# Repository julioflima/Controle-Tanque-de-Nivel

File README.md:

# Controle Tanque de Nível
## Projeto de Controle de Sistemas Dinâmicos - Engenharia Elétrica  - UFC

  Este projeto destina-se ao desenvolvimento de um controle de tanque de nível utilizando os conceitos de malha fechada. Como conrolador e sensor foram escolhidos respectivamente, o ATMEGA168-P e o HC-SR04.

  Os sistemas automáticos de níveis de água atualmente estão presentes em boa parte no cotidiano da vida humana, sejam em industrias ou mesmo nas casas, tendo em vista os conceitos de reutilização ou captação de água. Para controlar estes tipos de sistemas, geralmente utilizam-se de sensores de nível para acionamento da bomba e o controle pode ser feito a partir de um controlador PID ou por histerese, por exemplo. O relatório referente a este projeto se limitará à um controle realizado com base na histerese de sistemas de controle, nos quais os procedimentos serão apresentados mais adiante. A figura abaixo mostra um exemplo esquemático de um sistema hidráulico controlado pela bomba.

  Para o sistema controlado, a histerese é implementada na forma dinâmica de um determinado atraso da saída em referência com a entrada, desde que esta seja lentamente variável. Este tipo de histerese é uma relação de dependência de taxas, ou seja, pode funcionar com sistemas que necessitem de armazenamento durável de memória. Esta técnica como controlador serve basicamente para filtragem de sinais a fim de que se obtenha uma saída mais lenta de acordo com a memória armazenada de um sinal mais recente. 
Em um sistema baseado em ações liga/desliga, este controle reduz a vida útil ou afeta os dispositivos conectados a este sistema. Por isso, a utilização da técnica de histerese torna-se interessante para sistemas do tipo, resultando, assim, em uma seleção de uma determinada faixa, por exemplo com temperatura, como mostra abaixo.

  A IHM desenvolvida, teve como intuito a facilidade na hora de interagir na mudança do valor de referência e na visualização do nível atual do tanque independentemente da medição analógica, essa por meio de um duto transparente. Nela foi utilizada um display LCD 16x2, onde é possível a verificação dos valores. Dois botões para mudança no valor da referência. Dois barramentos, um destinado ao sensor ultrassônico, e o outro destinado a placa de driver. Uma saída seria, onde os valores de PWM, nível do tanque e valore de referência, são enviados ao computador para análise. Assim como o micro controlador ATMEGA328-P, responsável pelo controle e aquisição de dados. O esquemático e a placa discorrida nesta seção encontra-se nos anexos do relatório.

  O sensor utilizado neste projeto é o sensor ultrassônico HC-SR04, utilizado para medir distâncias entre 2cm até 4m. Com o intuito de fixação na estrutura desenvolvia, o sensor foi encapsulado em um case como mostra a figura abaixo. O esquemático discorrido nesta seção, assim como mais detalhes encontra-se nos anexos do relatório.

  O driver representa a parte de potência de um projeto, sendo este responsável pelo chaveamento de uma alta corrente, pois o controlador não suporta esse nível de potência, sendo assim indispensável. A placa de controle desenvolvida segue abaixo na figura abaixo.

  Segue abaixo os gráficos relativos a dinâmica desse sistema, com o controle desenvolvido até então. Em verde o PWM, em vermelho a referência e em azul a elevação do nível da água.

## FORK IT!

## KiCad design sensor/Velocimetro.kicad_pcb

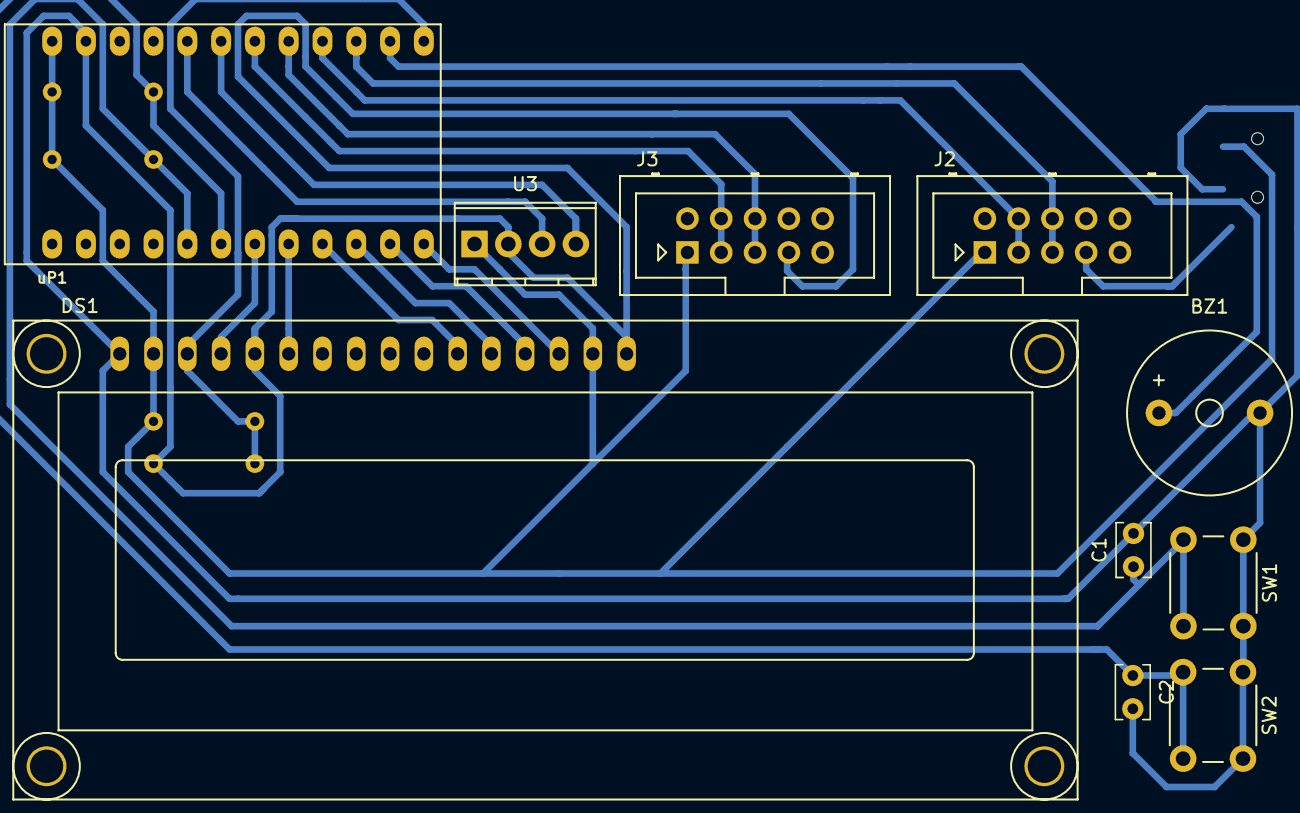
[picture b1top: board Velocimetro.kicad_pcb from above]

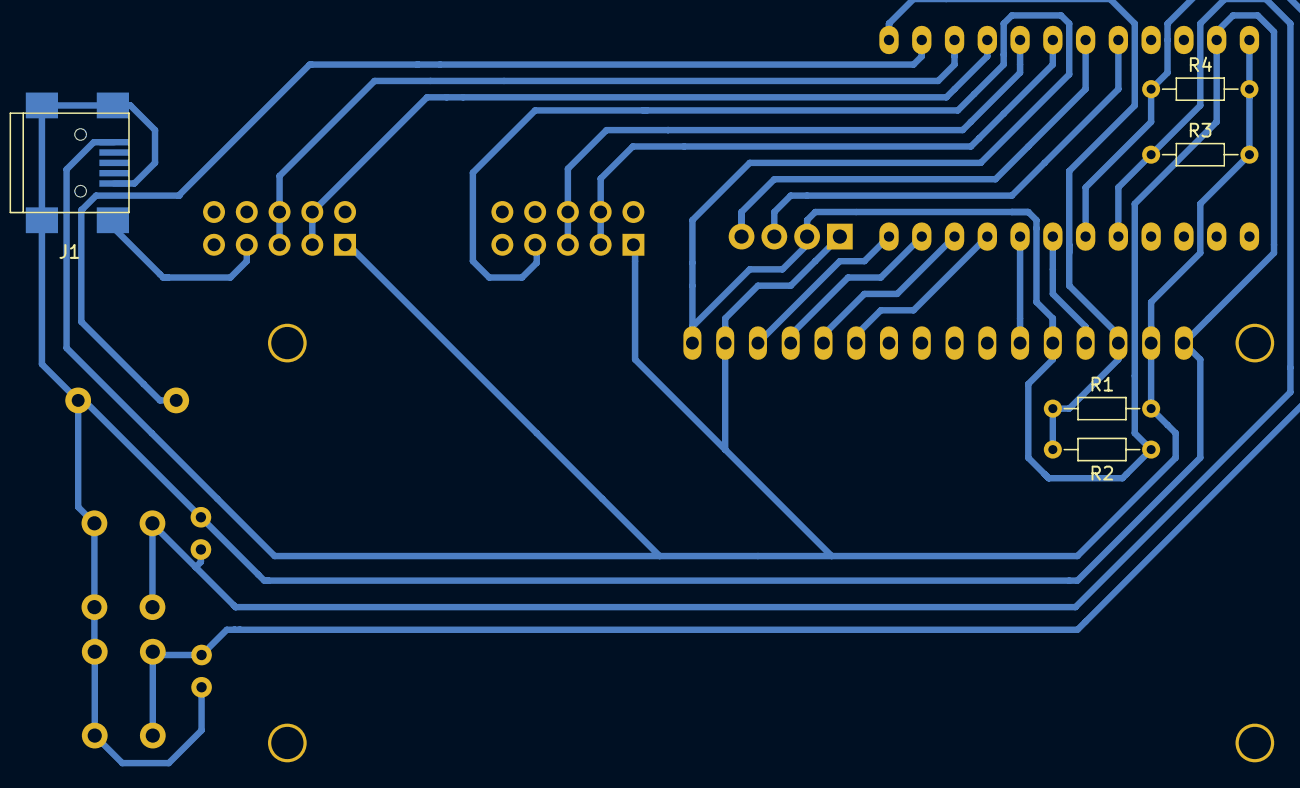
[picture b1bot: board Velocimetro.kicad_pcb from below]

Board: 2 copper layers, 15 parts (5 on the bottom side), 18 nets.

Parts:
BZ1: Buzzer; Buzzer_12x9.5RM7.6
C1, C2: 100n; C_Rect_L4.0mm_W2.5mm_P2.50mm
DS1: LCD16X2; WC1602A
J1: USB_OTG; USB_Mini-B
J2, J3: Conn_02x05_Odd_Even; Multicomp_MC9A12-1034_2x05x2.54mm_Straight
R1: 22k; R_Axial_DIN0204_L3.6mm_D1.6mm_P7.62mm_Horizontal
R2, R3, R4: 1k; R_Axial_DIN0204_L3.6mm_D1.6mm_P7.62mm_Horizontal
SW1, SW2: SW_DIP_x01; SW_PUSH_6mm
U3: HC-05; TerminalBlock_Phoenix_MPT-2.54mm_4pol
uP1: arduino_pro_mini; pro_mini

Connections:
+5V: DS1.2, DS1.15, J1.1, J2.1, J3.1, R1.2, R3.2, R4.2, U3.1, uP1.24
GND: BZ1.2, C1.2, C2.2, DS1.1, DS1.5, DS1.16, J1.5, J1.6, J2.7, J3.7, R2.1, SW1.1, SW2.1, U3.2, uP1.23
blue-RXD: U3.4, uP1.19
blue-TXD: U3.3, uP1.20
btn-1: C1.1, R3.1, SW1.2, uP1.5
btn-2: C2.1, R4.1, SW2.2, uP1.6
buzzer: BZ1.1, uP1.14
d4: DS1.11, uP1.9
d5: DS1.12, uP1.10
d6: DS1.13, uP1.11
d7: DS1.14, uP1.12
e: DS1.6, uP1.8
rs: DS1.4, uP1.7
uS01-2: J2.3, J2.4, uP1.16
uS01-3: J2.5, J2.6, uP1.15
uS02-2: J3.3, J3.4, uP1.18
uS02-3: J3.5, J3.6, uP1.17
v0: DS1.3, R1.1, R2.2, uP1.13

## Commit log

2017-12-16 init
2017-12-16 add control
2017-12-16 creat readme
2017-12-16 add images
2017-12-16 edit 1
2017-12-16 finit
2017-12-16 edit 2
2017-12-16 edit 3
2017-12-16 fix uc
2017-12-16 REPORT
